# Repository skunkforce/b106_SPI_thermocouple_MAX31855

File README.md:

# edgy_board number b106
This design is part of the [edgy board project](https://github.com/skunkforce/edgy_boards).

# getting started
This repository uses submodules. After cloning use the command 

```$ git submodule update --init --recursive```

to pull the submodules before opening the project with kicad. 

# Tests
Tests can be found in [TESTS.md](TESTS.md)

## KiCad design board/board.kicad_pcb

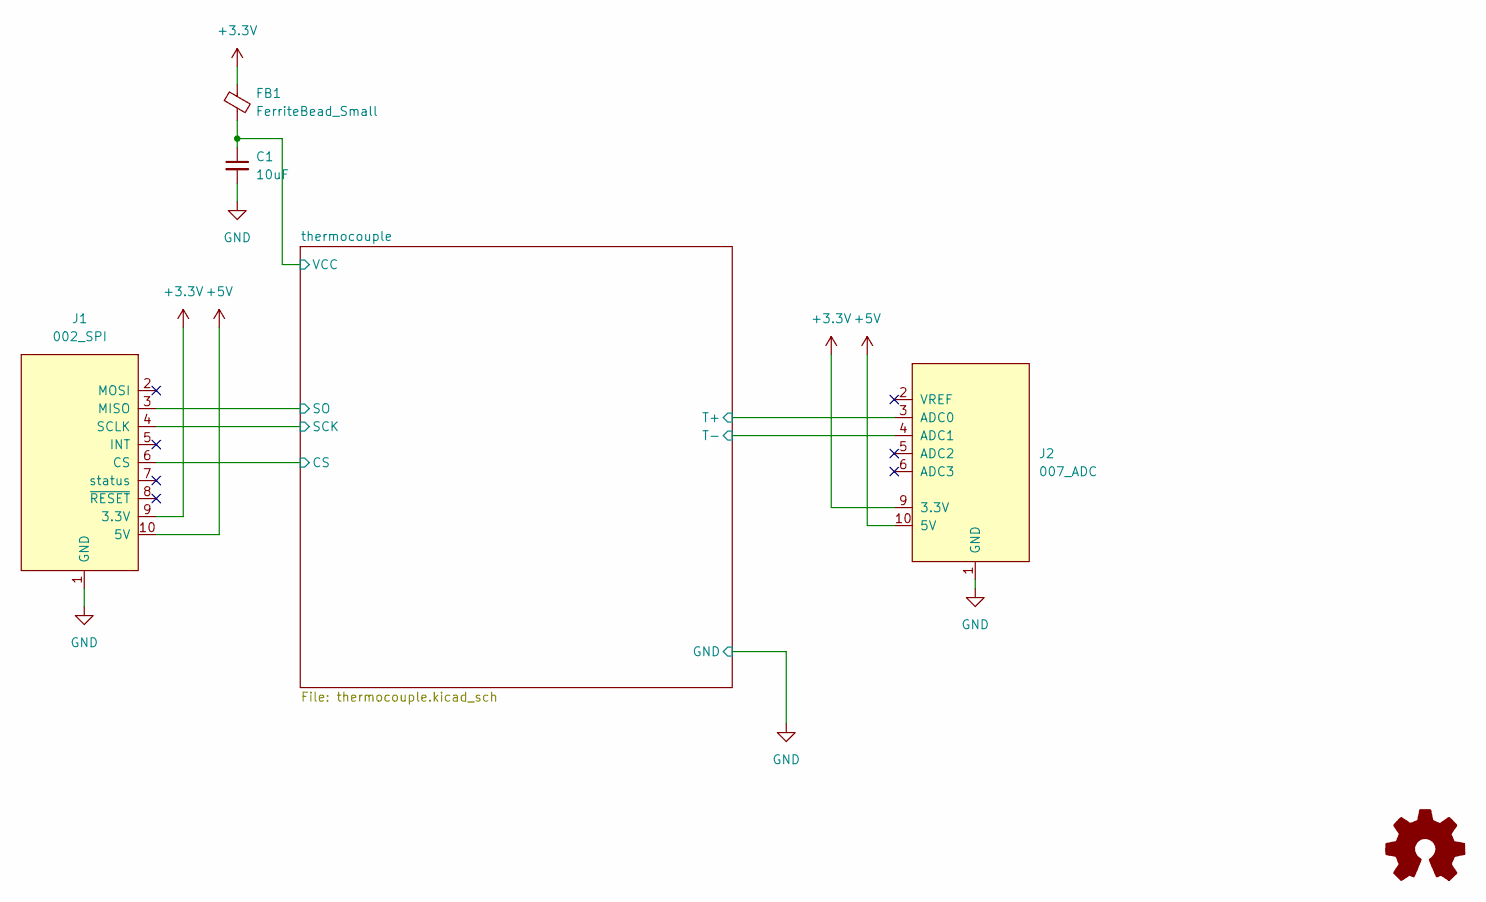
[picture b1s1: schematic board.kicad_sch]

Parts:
C1: 10uF; C_0603_1608Metric
FB1: FerriteBead_Small; L_0603_1608Metric
J1: 002_SPI; on_edge_2x05_device
J2: 007_ADC; on_edge_2x05_host
LOGO1: Logo_Open_Hardware_Small; OSHW-Symbol_6.7x6mm_SilkScreen

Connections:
+3.3V: FB1.1, J1.9 (3.3V), J2.9 (3.3V)
+5V: J1.10 (5V), J2.10 (5V)
/thermocouple/CS: J1.6 (CS); also elsewhere on the board
/thermocouple/SCK: J1.4 (SCLK); also elsewhere on the board
/thermocouple/SO: J1.3 (MISO); also elsewhere on the board
/thermocouple/T+: J2.3 (ADC0); also elsewhere on the board
/thermocouple/T-: J2.4 (ADC1); also elsewhere on the board
/thermocouple/VCC: C1.1, FB1.2; also elsewhere on the board
GND: C1.2, J1.1 (GND), J2.1 (GND); also elsewhere on the board

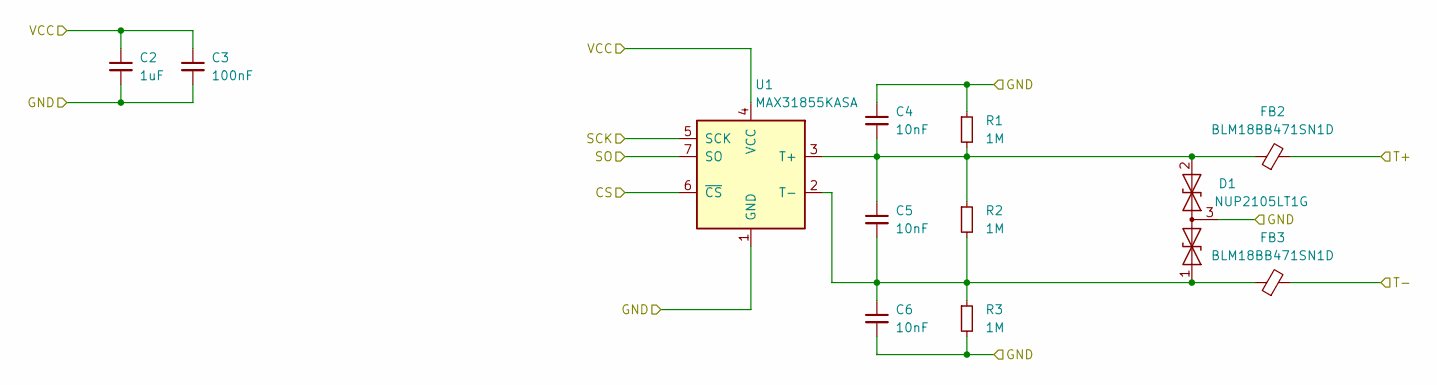
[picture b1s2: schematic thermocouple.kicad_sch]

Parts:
C2: 1uF; C_0603_1608Metric
C3: 100nF; C_0603_1608Metric
C4, C5, C6: 10nF; C_0603_1608Metric
D1: NUP2105LT1G; SOT-23; MPN NUP2105LT1G
FB2, FB3: BLM18BB471SN1D; L_0603_1608Metric
R1, R2, R3: 1M; R_0603_1608Metric
U1: MAX31855KASA; SOIC-8_3.9x4.9mm_P1.27mm

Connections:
/thermocouple/CS: U1.6 (~CS); also elsewhere on the board
/thermocouple/SCK: U1.5 (SCK); also elsewhere on the board
/thermocouple/SO: U1.7 (SO); also elsewhere on the board
/thermocouple/T+: FB2.2; also elsewhere on the board
/thermocouple/T-: FB3.2; also elsewhere on the board
/thermocouple/VCC: C2.1, C3.1, U1.4 (VCC); also elsewhere on the board
GND: C2.2, C3.2, C4.1, C6.2, D1.3 (common), R1.1, R3.2, U1.1 (GND); also elsewhere on the board
unnamed: C4.2, C5.1, D1.2 (A2), FB2.1, R1.2, R2.1, U1.3 (T+)
unnamed: C5.2, C6.1, D1.1 (A1), FB3.1, R2.2, R3.1, U1.2 (T-)

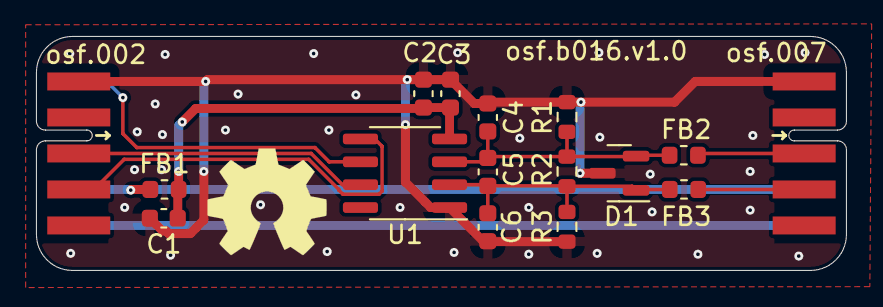
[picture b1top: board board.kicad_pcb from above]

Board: 2 copper layers, 45.0 x 13.0 mm, 17 parts (0 on the bottom side), 11 nets.

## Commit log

2023-03-06 initial
2023-03-29 added copper pours
